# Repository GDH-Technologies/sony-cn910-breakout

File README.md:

# sony-cn910-breakout

Repository for schematics and PCBs for using Sony Camcorders with the VC-195 board and CN910 FPC service port.

The full version is for connecting to the service ports (CN910) of my sony handycams and 1. amplifying the FM RF signal for `vhs-decode` and 2. using a raspberry pi to interface with the camcorder via LANC.

The simplified version is simply meant to give me the ability to connect to the camcorder's FM RF output for external amplification. Only the `PB RF`, `REC RF`, and `REG GND` pins of CN910 are available for connection via SMA jack. A few other CN910 signals have test points, but the FM RF signals are the only ones with an SMA connection.

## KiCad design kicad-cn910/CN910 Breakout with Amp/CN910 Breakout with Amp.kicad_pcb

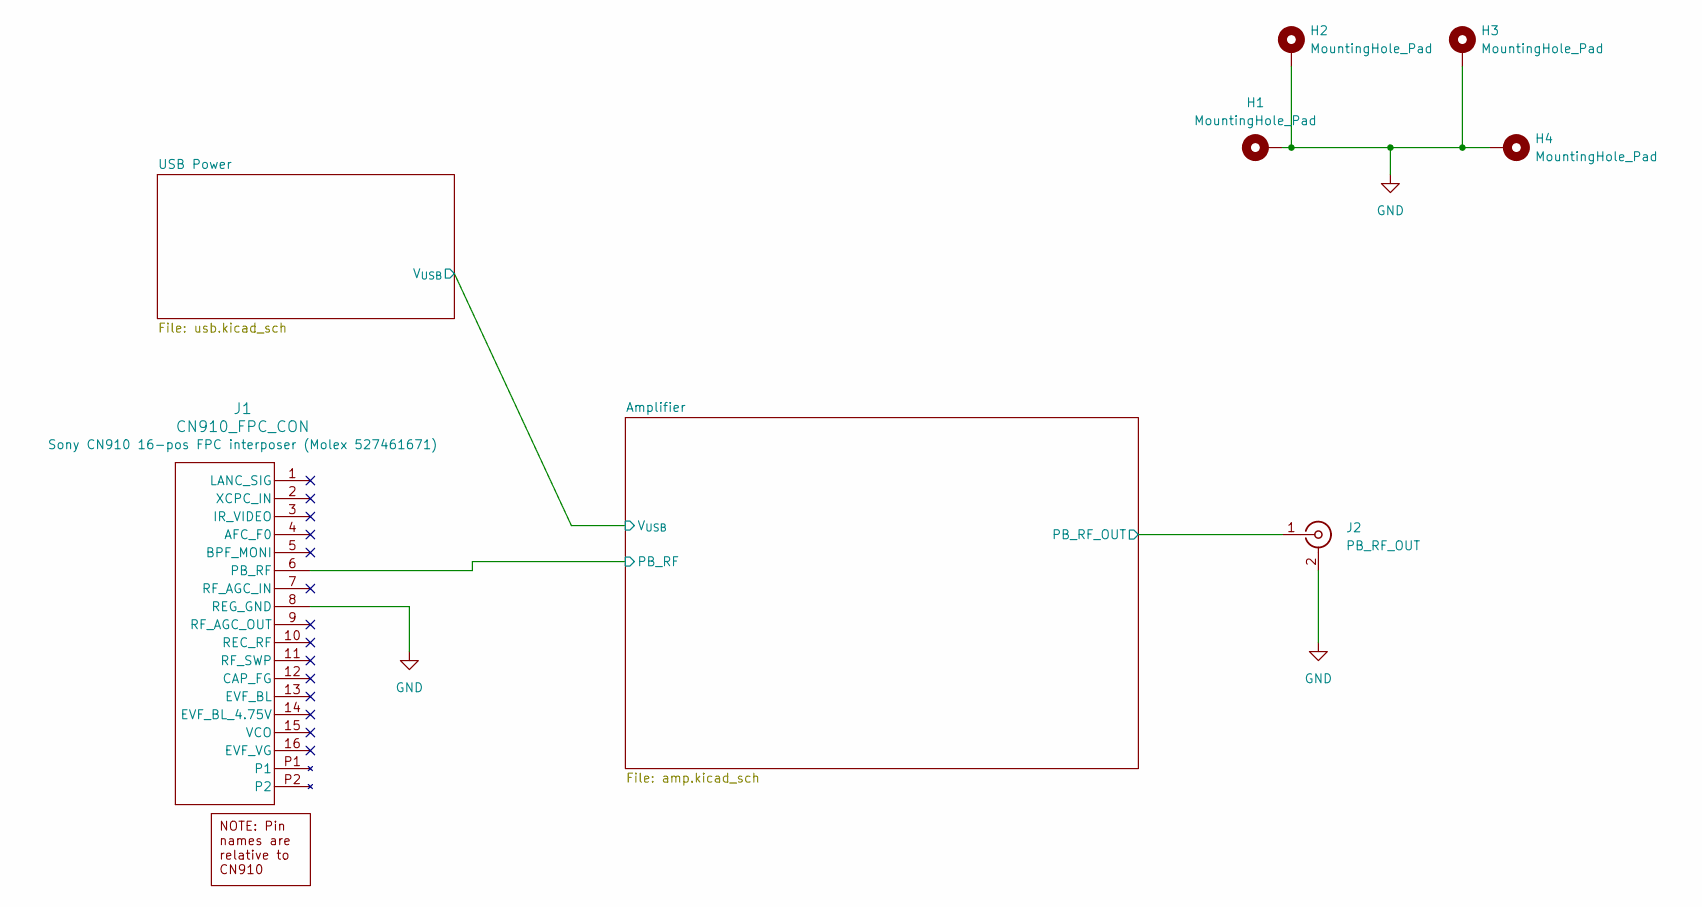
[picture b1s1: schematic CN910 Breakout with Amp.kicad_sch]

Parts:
H1, H2, H3, H4: MountingHole_Pad; MountingHole_2.2mm_M2_Pad_TopBottom
J1: CN910_FPC_CON; CON_527461671_MOL; MPN 527461671
J2: PB_RF_OUT; Molex_0731000154_BNC_RA_THT

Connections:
/Amplifier/PB_RF: J1.6 (PB_RF); also elsewhere on the board
/Amplifier/PB_RF_OUT: J2.1 (In); also elsewhere on the board
GND: H1.1 (1_1), H2.1 (1_1), H3.1 (1_1), H4.1 (1_1), J1.8 (REG_GND), J2.2 (Ext); also elsewhere on the board

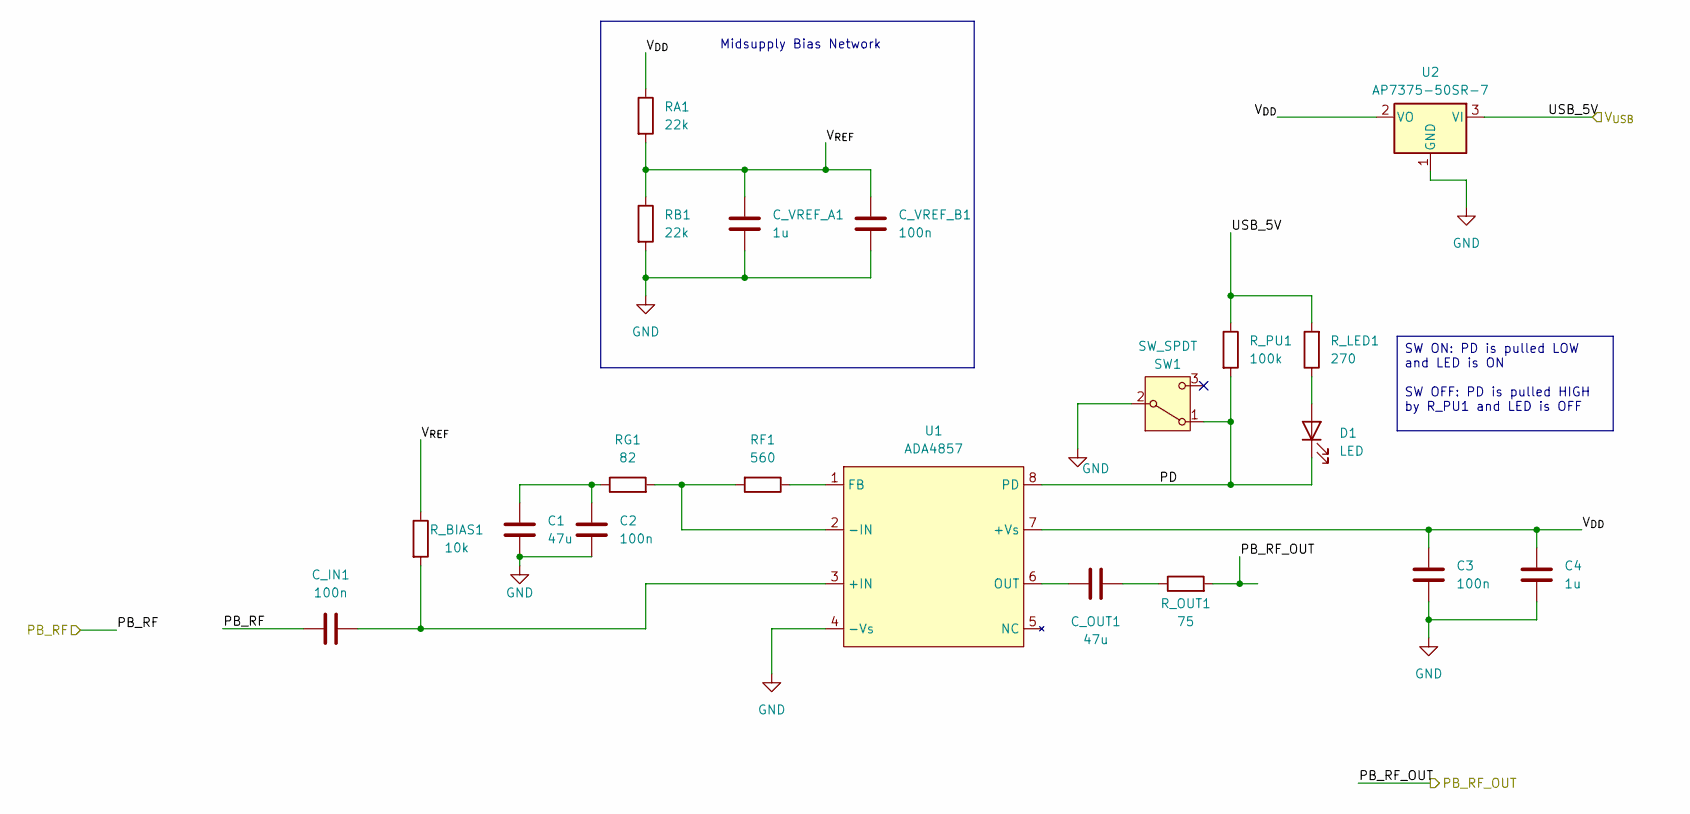
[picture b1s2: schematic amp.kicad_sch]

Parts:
C1: 47u; C_1206_3216Metric_Pad1.33x1.80mm_HandSolder
C2, C3: 100n; C_0603_1608Metric_Pad1.08x0.95mm_HandSolder
C4: 1u; C_0603_1608Metric_Pad1.08x0.95mm_HandSolder
C_IN1: 100n; C_0603_1608Metric_Pad1.08x0.95mm_HandSolder
C_OUT1: 47u; C_1206_3216Metric_Pad1.33x1.80mm_HandSolder; MFR.Part CL31A476MPHNNNE; LCSC C96123
C_VREF_A1: 1u; C_0603_1608Metric_Pad1.08x0.95mm_HandSolder
C_VREF_B1: 100n; C_0603_1608Metric_Pad1.08x0.95mm_HandSolder
D1: LED; LED_0805_2012Metric_Pad1.15x1.40mm_HandSolder
RA1: 22k; R_0805_2012Metric_Pad1.20x1.40mm_HandSolder
RB1: 22k; R_0805_2012Metric_Pad1.20x1.40mm_HandSolder
RF1: 560; R_0805_2012Metric_Pad1.20x1.40mm_HandSolder
RG1: 82; R_0805_2012Metric_Pad1.20x1.40mm_HandSolder
R_BIAS1: 10k; R_0805_2012Metric_Pad1.20x1.40mm_HandSolder
R_LED1: 270; R_0805_2012Metric_Pad1.20x1.40mm_HandSolder
R_OUT1: 75; R_0805_2012Metric_Pad1.20x1.40mm_HandSolder; MFR.Part 0603WAF750JT5E; LCSC C4275
R_PU1: 100k; R_0805_2012Metric_Pad1.20x1.40mm_HandSolder
SW1: SW_SPDT; Slide_Switch_SS12D07_CNK
U1: ADA4857; ADA4857-1YRZ-R7; MFR.Part ADA4857-1YRZ-R7; LCSC C208021
U2: AP7375-50SR-7; SOT-23-3

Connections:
/Amplifier/PB_RF: C_IN1.1; also elsewhere on the board
/Amplifier/PB_RF_OUT: R_OUT1.2; also elsewhere on the board
/Amplifier/PD: D1.1 (K), R_PU1.2, SW1.1 (A), U1.8 (PD)
/Amplifier/USB_5V: R_LED1.2, R_PU1.1, U2.3 (VI); also elsewhere on the board
/Amplifier/V_{DD}: C3.1, C4.1, RA1.1, U1.7 (+Vs), U2.2 (VO)
/Amplifier/V_{REF}: C_VREF_A1.1, C_VREF_B1.2, RA1.2, RB1.1, R_BIAS1.1
GND: C1.2, C2.2, C3.2, C4.2, C_VREF_A1.2, C_VREF_B1.1, RB1.2, SW1.2 (B), U1.4 (-Vs), U2.1 (GND); also elsewhere on the board
unnamed: C1.1, C2.1, RG1.1
unnamed: C_OUT1.1, R_OUT1.1
unnamed: D1.2 (A), R_LED1.1
unnamed: C_IN1.2, R_BIAS1.2, U1.3 (+IN)
unnamed: RF1.2, RG1.2, U1.2 (-IN)
unnamed: RF1.1, U1.1 (FB)
unnamed: C_OUT1.2, U1.6 (OUT)

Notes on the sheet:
Midsupply Bias Network
SW ON: PD is pulled LOW and LED is ON SW OFF: PD is pulled HIGH by R_PU1 and LED is OFF

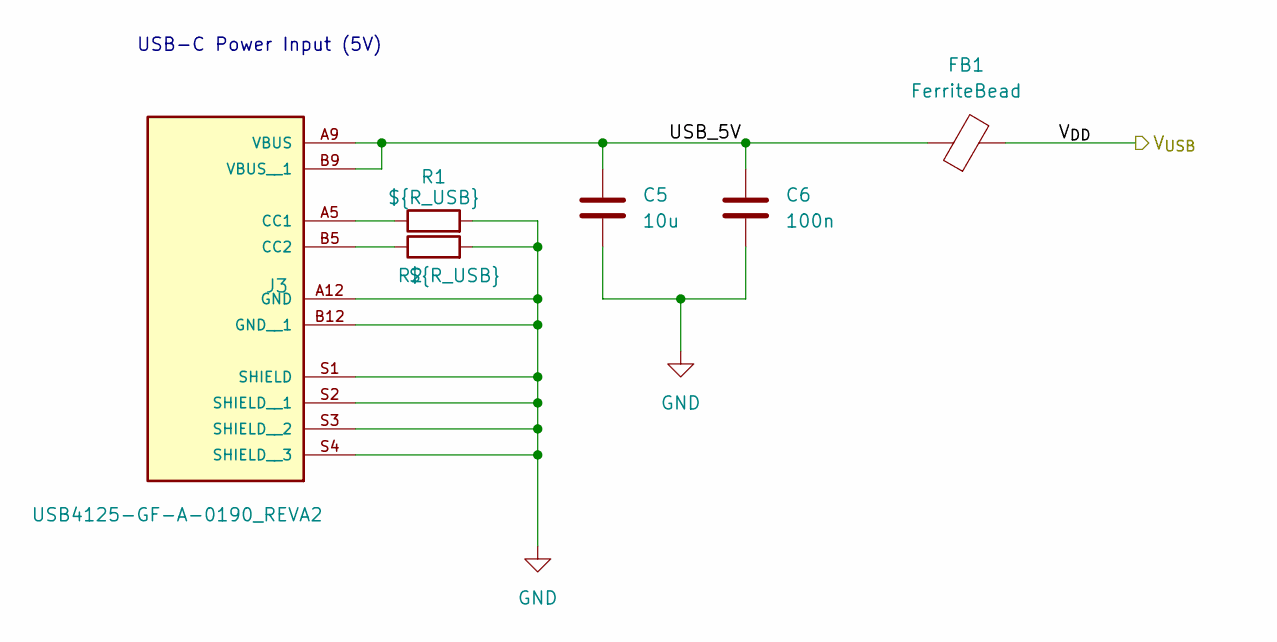
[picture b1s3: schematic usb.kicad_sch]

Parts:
C5: 10u; C_0603_1608Metric_Pad1.08x0.95mm_HandSolder
C6: 100n; C_0603_1608Metric_Pad1.08x0.95mm_HandSolder
FB1: FerriteBead; L_1206_3216Metric_Pad1.22x1.90mm_HandSolder
J3: USB4125-GF-A-0190_REVA2; GCT_USB4125-GF-A-0190_REVA2; PARTREV Rev A2
R1, R2: ${R_USB}; R_0805_2012Metric_Pad1.20x1.40mm_HandSolder

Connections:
/Amplifier/USB_5V: FB1.2; also elsewhere on the board
/USB Power/USB_5V: C5.1, C6.1, FB1.1, J3.A9 (VBUS), J3.B9 (VBUS__1)
GND: C5.2, C6.2, J3.A12 (GND), J3.B12 (GND__1), J3.S1 (SHIELD), J3.S2 (SHIELD__1), J3.S3 (SHIELD__2), J3.S4 (SHIELD__3), R1.2, R2.2; also elsewhere on the board
unnamed: J3.A5 (CC1), R1.1
unnamed: J3.B5 (CC2), R2.1

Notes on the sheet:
USB-C Power Input (5V)

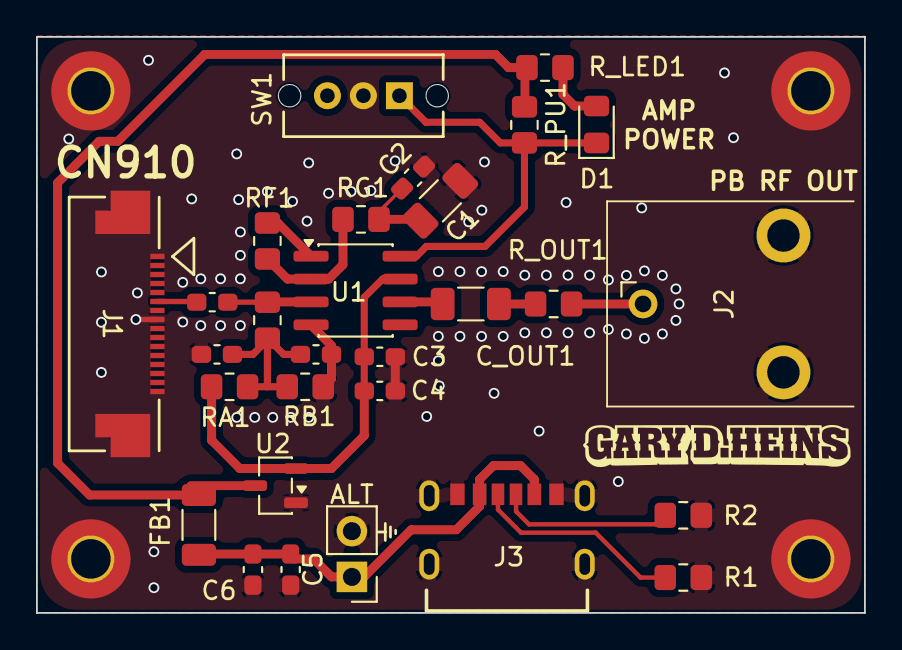
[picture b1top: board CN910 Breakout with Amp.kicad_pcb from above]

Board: 2 copper layers, 46.0 x 32.0 mm, 33 parts (0 on the bottom side), 17 nets.

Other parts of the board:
SONY_AMP**: Board

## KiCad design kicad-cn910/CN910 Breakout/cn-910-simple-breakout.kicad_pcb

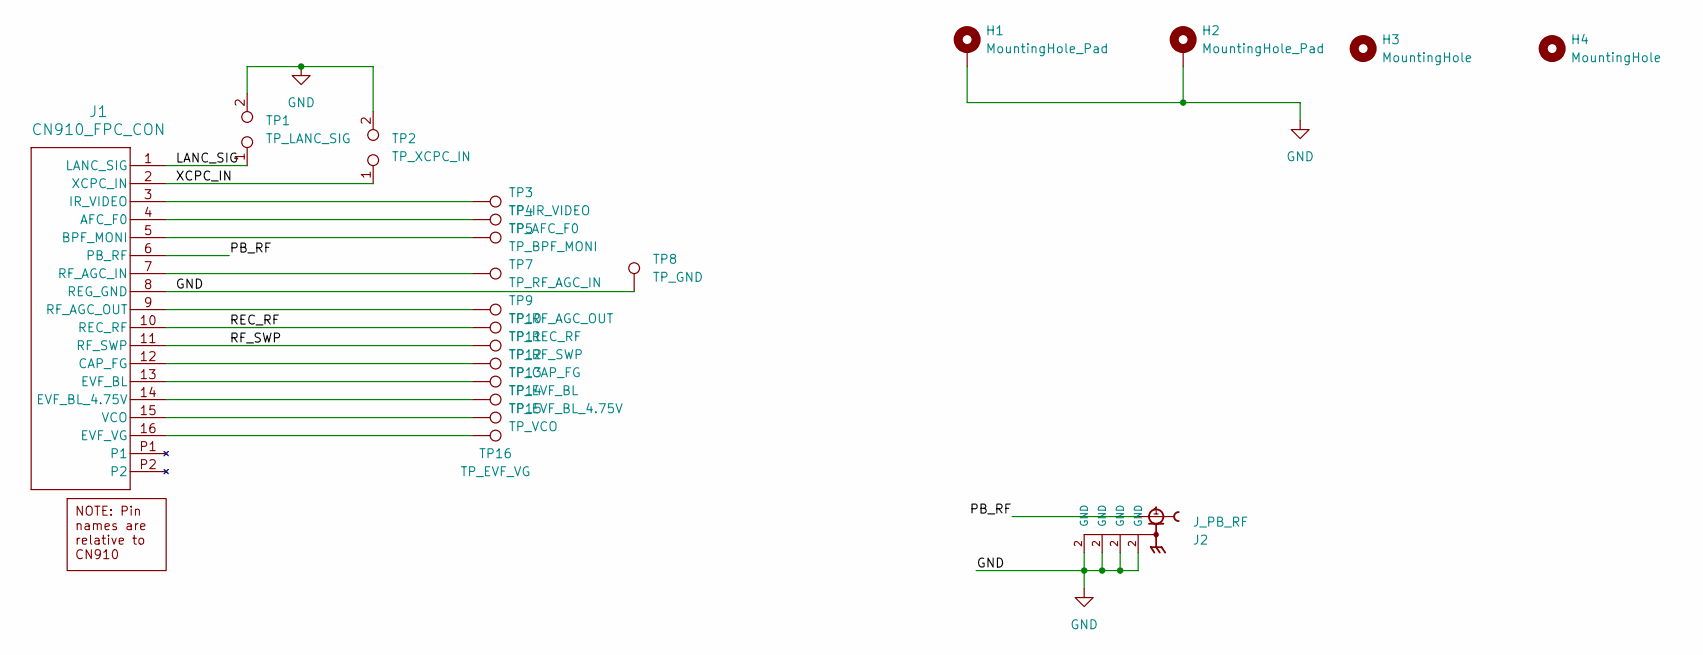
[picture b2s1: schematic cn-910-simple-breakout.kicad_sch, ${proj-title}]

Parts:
H1, H2: MountingHole_Pad; MountingHole_2.2mm_M2_ISO14580_Pad
H3, H4: MountingHole; MountingHole_2.2mm_M2_ISO14580
J1: CN910_FPC_CON; CON_527461671_MOL; MPN 527461671
J2: J_PB_RF; SMA_Samtec_SMA-J-P-H-ST-EM1_EdgeMount; PARTREV 1.0
TP1: TP_LANC_SIG; PinHeader_1x02_P2.54mm_Vertical
TP2: TP_XCPC_IN; PinHeader_1x02_P2.54mm_Vertical
TP3: TP_IR_VIDEO; TestPoint_Pad_D1.5mm
TP4: TP_AFC_F0; TestPoint_Pad_D1.5mm
TP5: TP_BPF_MONI; TestPoint_Pad_D1.5mm
TP7: TP_RF_AGC_IN; TestPoint_Pad_D1.5mm
TP8: TP_GND; TestPoint_Bridge_Pitch2.54mm_Drill1.3mm
TP9: TP_RF_AGC_OUT; TestPoint_Pad_D1.5mm
TP10: TP_REC_RF; TestPoint_Pad_D1.5mm
TP11: TP_RF_SWP; TestPoint_Pad_D1.5mm
TP12: TP_CAP_FG; TestPoint_Pad_D1.5mm
TP13: TP_EVF_BL; TestPoint_Pad_D1.5mm
TP14: TP_EVF_BL_4.75V; TestPoint_Pad_D1.5mm
TP15: TP_VCO; TestPoint_Pad_D1.5mm
TP16: TP_EVF_VG; TestPoint_Pad_D1.5mm

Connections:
/LANC_SIG: J1.1 (LANC_SIG), TP1.1
/PB_RF: J1.6 (PB_RF), J2.1
/REC_RF: J1.10 (REC_RF), TP10.1 (1_1)
/RF_SWP: J1.11 (RF_SWP), TP11.1 (1_1)
/XCPC_IN: J1.2 (XCPC_IN), TP2.1
GND: H1.1 (1_1), H2.1 (1_1), J1.8 (REG_GND), J2.2 (GND_2), TP1.2, TP2.2, TP8.1 (1_1)
unnamed: J1.4 (AFC_F0), TP4.1 (1_1)
unnamed: J1.5 (BPF_MONI), TP5.1 (1_1)
unnamed: J1.12 (CAP_FG), TP12.1 (1_1)
unnamed: J1.13 (EVF_BL), TP13.1 (1_1)
unnamed: J1.14 (EVF_BL_4.75V), TP14.1 (1_1)
unnamed: J1.16 (EVF_VG), TP16.1 (1_1)
unnamed: J1.3 (IR_VIDEO), TP3.1 (1_1)
unnamed: J1.7 (RF_AGC_IN), TP7.1 (1_1)
unnamed: J1.9 (RF_AGC_OUT), TP9.1 (1_1)
unnamed: J1.15 (VCO), TP15.1 (1_1)

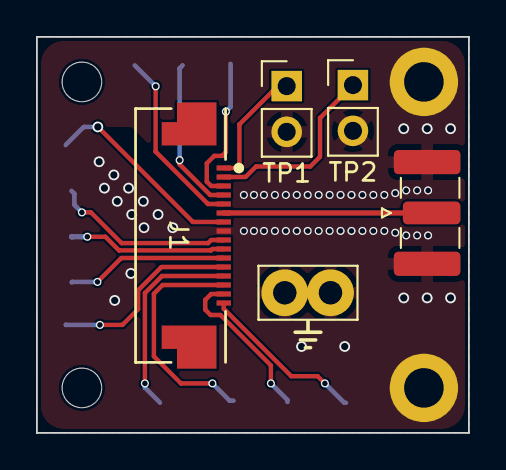
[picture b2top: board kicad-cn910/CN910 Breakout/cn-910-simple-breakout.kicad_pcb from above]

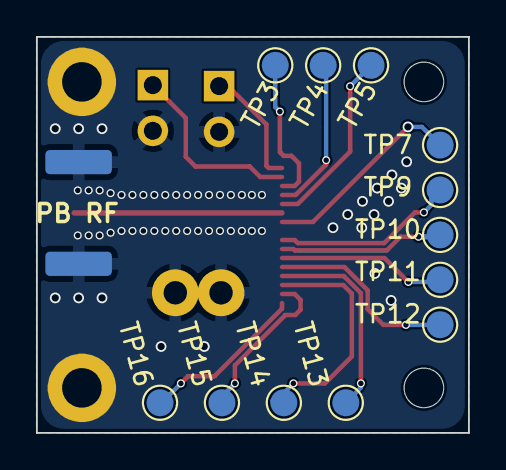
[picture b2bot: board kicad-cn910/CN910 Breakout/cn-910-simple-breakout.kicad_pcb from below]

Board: 2 copper layers, 24.0 x 22.0 mm, 22 parts (12 on the bottom side), 16 nets.

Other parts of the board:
SONY_SIMPLE**: Board

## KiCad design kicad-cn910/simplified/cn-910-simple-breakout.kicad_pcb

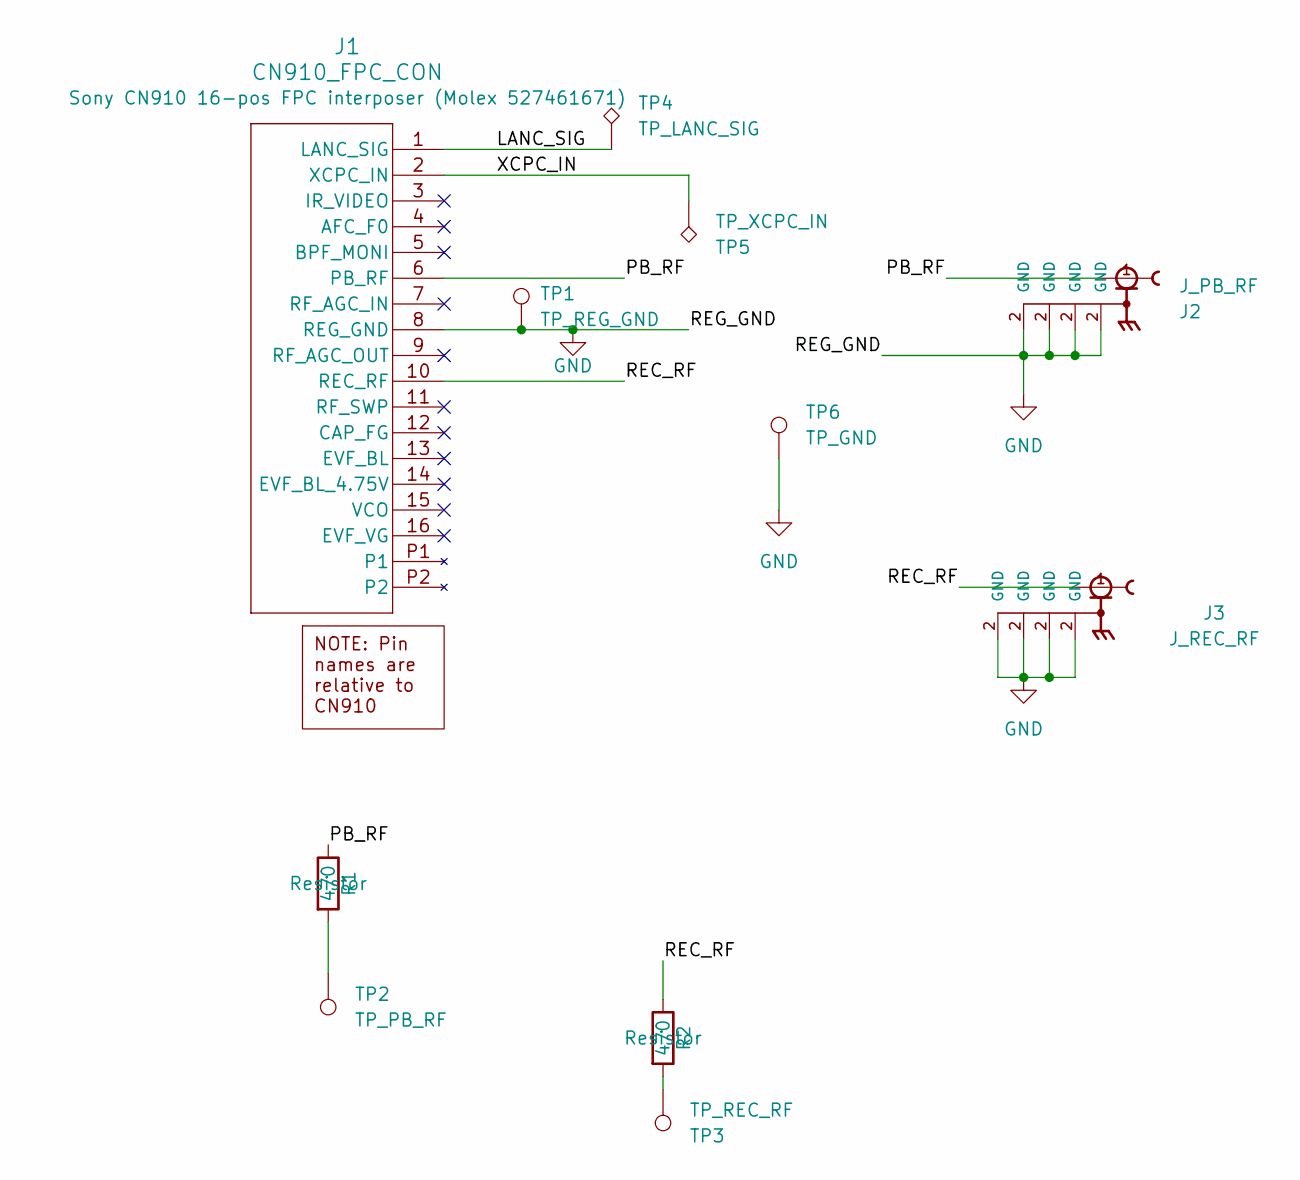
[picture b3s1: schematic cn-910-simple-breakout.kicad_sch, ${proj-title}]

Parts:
J1: CN910_FPC_CON; CON_527461671_MOL; MPN 527461671
J2: J_PB_RF; GRADCONN_RFPC-SMA28-F; PARTREV 1.0
J3: J_REC_RF; GRADCONN_RFPC-SMA28-F; PARTREV 1.0
R1, R2: 470; R_0603_1608Metric
TP1: TP_REG_GND; TestPoint_Bridge_Pitch2.54mm_Drill1.3mm
TP2: TP_PB_RF; TestPoint_Loop_D2.50mm_Drill1.0mm
TP3: TP_REC_RF; TestPoint_Loop_D2.50mm_Drill1.0mm
TP4: TP_LANC_SIG; TestPoint_Loop_D2.50mm_Drill1.0mm
TP5: TP_XCPC_IN; TestPoint_Loop_D2.50mm_Drill1.0mm
TP6: TP_GND; TestPoint_Loop_D2.50mm_Drill1.0mm

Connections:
/LANC_SIG: J1.1 (LANC_SIG), TP4.1 (1_1)
/PB_RF: J1.6 (PB_RF), J2.1, R1.1
/REC_RF: J1.10 (REC_RF), J3.1, R2.1
/XCPC_IN: J1.2 (XCPC_IN), TP5.1 (1_1)
GND: J1.8 (REG_GND), J2.2 (GND_2), J3.2 (GND_2), TP1.1 (1_1), TP6.1 (1_1)
unnamed: R1.2, TP2.1 (1_1)
unnamed: R2.2, TP3.1 (1_1)

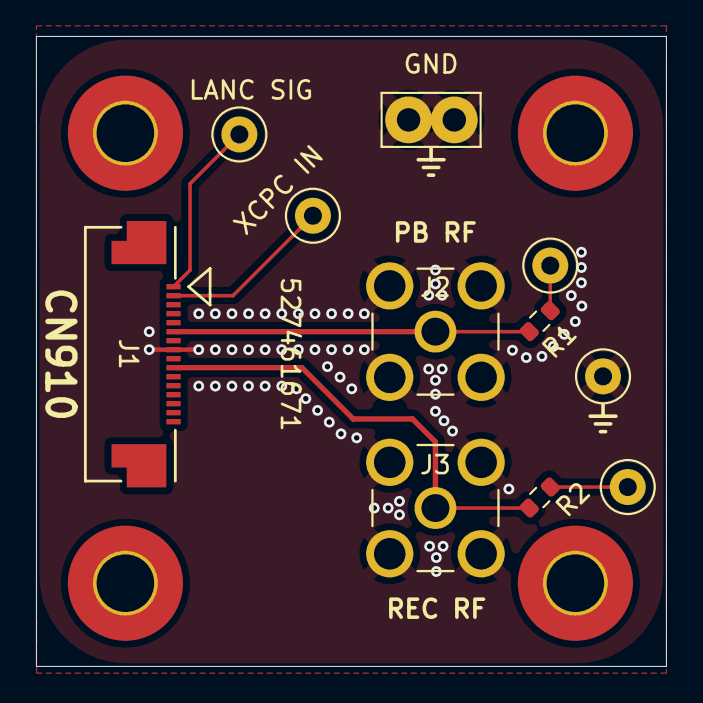
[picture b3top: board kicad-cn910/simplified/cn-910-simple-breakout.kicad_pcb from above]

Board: 2 copper layers, 35.0 x 35.0 mm, 11 parts (0 on the bottom side), 7 nets.

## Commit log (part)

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2026-04-22 Adding KiCad project
2026-04-23 PCB work
2026-04-23 Wired up scope checking SMA connectors
2026-04-24 LANC interface layout
2026-04-24 Nearly finalized Sony CN910 PCB and added archives of the modified clockgen main board and CX card jig
2026-04-28 Refined routing
2026-06-05 Updated KiCad project files for CN910 breakout, including version upgrades to 10.0, added new components, and refined design settings. Added .gitignore entries for KiCad artifacts and included a new 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
2026-06-05 Enhanced CN910 breakout KiCad project with updated design rules, added new components, and refined PCB layout. Introduced a new simple breakout PCB with detailed Gerber files for manufacturing. Updat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
2026-06-05 Updated interactive BOM for the CN910 breakout project, changing the title to "Sony CCD-TRV615 Amp BOM" and refining the configuration settings. Removed unused fields from the BOM configuration for i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
2026-06-06 Refactored CN910 breakout KiCad project files, updating footprint and symbol references to "GDH" naming convention. Adjusted PCB thickness and dielectric properties for improved design accuracy. Adde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
2026-06-06 Updated CN910 breakout KiCad project files with dynamic project metadata, including title, company, version, and license. Refined design rules and component properties for improved clarity and organi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
2026-06-06 Updated CN910 breakout KiCad project files to reflect JLCPCB manufacturing specifications, including revised design rules for track width, via dimensions, and hole clearances. Adjusted component prop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
2026-06-08 Add Gerber files and library tables for cn-910-simple-breakout project
    - Created new Gerber file for PTH drill: cn-910-simple-breakout-PTH-drl.gbr
    - Added job file for Gerber generation: cn-910-simple-breakout-job.gbrjob
    - Initialized footprint library table: fp-lib-table
    - Initialized symbol library table: sym-lib-table
2026-06-08 Update CN910 breakout PCB properties and add user text for Molex part number
2026-06-11 Refactor code structure for improved readability and maintainability
